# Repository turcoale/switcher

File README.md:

# switcher
Placa switcher, desarrollo de placa para automatización en instalaciones de frio

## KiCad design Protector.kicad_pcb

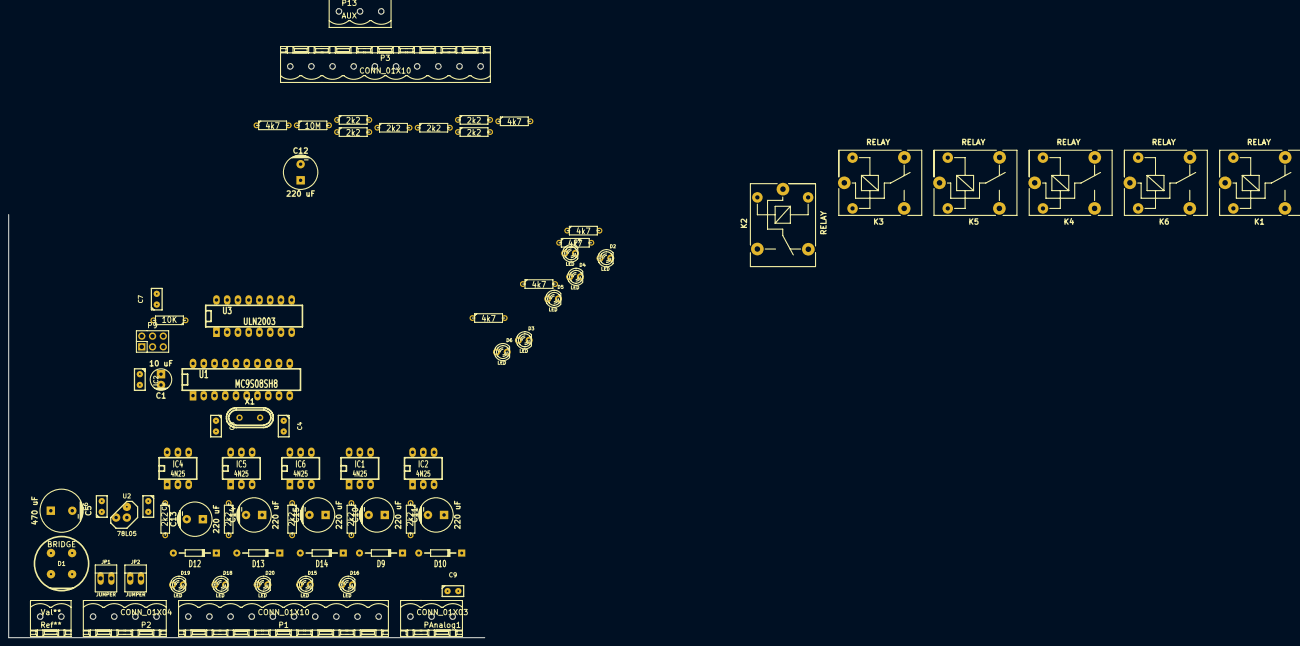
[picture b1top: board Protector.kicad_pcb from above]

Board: 2 copper layers, 75 parts (0 on the bottom side), 58 nets, no tracks yet.

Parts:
C1: 10 uF; Capacitor5x11RM2.5
C2, C9: 0,1 uF; Capacitor3MMDiscRM2.5
C3, C4: 22 nF; Capacitor3MMDiscRM2.5
C5: 470 uF; Capacitor10x16RM5
C6: 0.33 uF; Capacitor3MMDiscRM2.5
C7: 0.1 uF; Capacitor3MMDiscRM2.5
C8: 0.01 uF; Capacitor3MMDiscRM2.5
C10, C11, C12, C13, C14, C15: 220 uF; Capacitor8x21RM3.8
D1: BRIDGE; PUSH_BUTT_SHAPE1
D2, D3, D4, D5, D6, D7, D15, D16, D18, D19, D20: LED; LED-3MM
D9, D10, D12, D13, D14: 1N4001; Diode_DO-35_SOD27_Horizontal_RM10
IC1, IC2, IC4, IC5, IC6: 4N25; DIP-6__300_ELL
JP1, JP2: JUMPER; PINHEAD1-2
K1, K2, K3, K4, K5, K6: RELAY; Relay_SANYOU_SRD_Series_Form_C
P1, P3: CONN_01X10; PHOENIX_MSTBA2,54-G_10
P2: CONN_01X04; PHOENIX_MSTBA2,54-G_4
P9: BDM; Pin_Header_Straight_2x03
P13: AUX; PHOENIX_MSTBA2,54-G_3
PAnalog1: CONN_01X03; PHOENIX_MSTBA2,54-G_3
R1, R2, R4, R5, R6, R14, R15, R16, R17, R18, R19: 2k2; R3
R7, R8, R9, R10, R11, R12: 4k7; R3
R13: 10K; R3
R21: 10M; R3
Ref**: Val**; PHOENIX_MSTBA2,54-G_2
U1: MC9S08SH8; DIP-20__300_ELL
U2: 78L05; TO92-123
U3: ULN2003; DIP-16__300_ELL
X1: CRYSTAL; Crystal_HC49-U_Vertical

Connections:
/24Sen: JP1.1, P2.4, R4.2, R5.2, R6.2
/24V: C5.1, C6.1, D1.3, D2.1, D3.1, D4.1, D5.1, D6.1, D7.1, JP1.2, K1.2, K2.2, K3.2, K4.2, K5.2, K6.2, P2.2, U2.3, U3.9
/ADC: C9.1, PAnalog1.2, U1.19
/BDM: P9.1, U1.10
/COMSen: JP2.1, P1.1, P1.3, P1.5, P1.7, P1.9, P2.3
/EXTAL: C4.1, R21.1, U1.7, X1.2
/In1: IC4.5, R10.2
/In2: IC5.5, R11.2, U1.11
/In3: IC6.5, R12.2, U1.12
/In4: IC1.5, R7.2, U1.13
/In5: IC2.5, R8.2, U1.18
/OPT1: C13.2, D12.1, D19.2, IC4.2, P1.10
/OPT2: C14.2, D13.1, D18.2, IC5.2, P1.8
/OPT3: C15.2, D14.1, D20.2, IC6.2, P1.6
/OPT4: C10.2, D9.1, D15.2, IC1.2, P1.4
/OPT5: C11.2, D10.1, D16.2, IC2.2, P1.2
/Out1: U1.14, U3.6
/Out2: U1.15, U3.5
/Out3: U1.16, U3.4
/Out4: U1.17, U3.3
/Out5: U1.4, U3.2
/OutAux: U1.5, U3.1
/R1: K2.5, R15.2, U3.15
/R2: K3.5, R16.2, U3.14
/R3: K4.5, R17.2, U3.13
/R4: K5.5, R18.2, U3.12
/R5: K6.5, R19.2, U3.11
/RAUX: K1.5, R14.2, U3.16
/RESET: C7.1, P9.4, R13.2
/XTAL: C3.1, R21.2, U1.6, X1.1
/vreg: C1.1, C2.1, C8.1, P9.6, PAnalog1.3, R7.1, R8.1, R9.1, R10.1, R11.1, R12.1, R13.1, U1.9, U2.1
GND: C1.2, C2.2, C3.2, C4.2, C5.2, C6.2, C7.2, C8.2, C9.2, D1.2, IC1.4, IC2.4, IC4.4, IC5.4, IC6.4, JP2.2, P2.1, P9.2, PAnalog1.1, U1.8, U2.2, U3.8
unnamed: D1.1, Ref**.2
unnamed: D1.4, Ref**.1
unnamed: D2.2, R14.1
unnamed: D3.2, R15.1
unnamed: D4.2, R16.1
unnamed: D5.2, R17.1
unnamed: D6.2, R18.1
unnamed: D7.2, R19.1
unnamed: D15.1, IC1.1, R1.1
unnamed: D16.1, IC2.1, R2.1
unnamed: D18.1, IC5.1, R5.1
unnamed: D19.1, IC4.1, R4.1
unnamed: D20.1, IC6.1, R6.1
unnamed: K1.1, P13.2
unnamed: K1.3, P13.1
unnamed: K1.4, P13.3
unnamed: K2.1, P3.1
unnamed: K2.4, P3.2
unnamed: K3.1, P3.3
unnamed: K3.4, P3.4
unnamed: K4.1, P3.5
unnamed: K4.4, P3.6
unnamed: K5.3, P3.7
unnamed: K5.4, P3.8
unnamed: K6.1, P3.9
unnamed: K6.4, P3.10

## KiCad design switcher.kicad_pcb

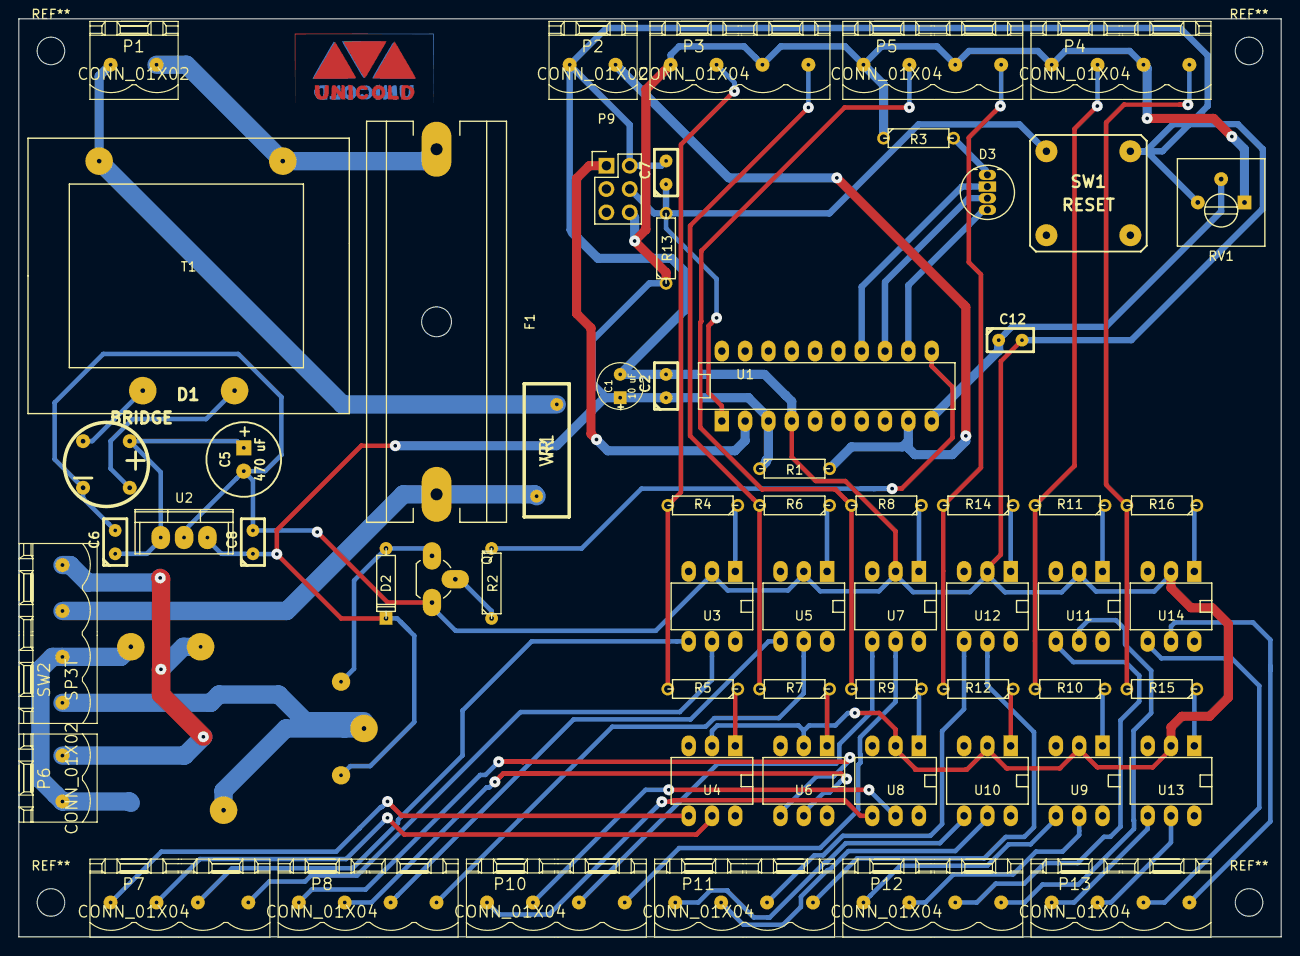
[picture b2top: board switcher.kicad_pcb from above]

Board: 2 copper layers, 137.5 x 100.0 mm, 61 parts (1 on the bottom side), 64 nets.

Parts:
C1: 10 uF; C1V5
C2, C12: 0,1 uF; C1
C5: 470 uF; C1V8
C6: 0.33 uF; C1
C7: 0.1 uF; C1
C8: 0.01 uF; C1
D1: BRIDGE; Bridge-rond
D2: 1N4001; D3
D3: Led_RGB_CA; LED-RGB-5MM_Common_Cathode
F1: FUSE; Fuseholder6x32_Horiz_Open_Schurter0031-8002
K1: RELAY; RELAY-HJQ-15F
P1, P2, P6: CONN_01X02; PHOENIX_MSTBA2,54-G_2
P3, P4, P5, P7, P8, P10, P11, P12, P13: CONN_01X04; PHOENIX_MSTBA2,54-G_4
P9: BDM; Pin_Header_Straight_2x03
Q1: BC237; TO-92_Rugged
R1: 10k; R3
R2, R3: 1k; R3
R4, R5, R6, R7, R8, R9, R10, R11, R12, R14, R15, R16: 220; R3
R13: 10K; R3
RV1: POT; Potentiometer_Trimmer-Suntan-TSR-3386P
SW1: RESET; sw_push4p
SW2: SP3T; PHOENIX_MSTBA2,54-G_4
T1: TRANSFO; TFCOBSIL2209VCA200mA
U1: MC9S08SH8; DIP-20__300_ELL
U2: 78L05; TO-220
U3, U4, U5, U6, U7, U8, U9, U10, U11, U12, U13, U14: 4N25; DIP-6__300_ELL
VR1: VR; SIOV-S20K150

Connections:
/24V: C5.1, C6.1, D1.3, U2.1
/BDM: P9.1, U1.2
/C: K1.3, K1.6, SW2.1
/F1: F1.2, SW2.3, VR1.1
/L: F1.1, P1.2, T1.1
/N: P1.1, T1.2, VR1.2
/NA: K1.2, P6.2, SW2.4
/NC: K1.1, P6.1, SW2.2
/RESET: C7.1, P9.4, R13.2, SW1.1, U1.1
/ST: C12.1, RV1.2, U1.10
/vreg: C1.1, C2.1, C8.1, D2.1, K1.5, P3.1, P3.3, P4.1, P4.3, P5.1, P5.3, P9.6, R1.1, R3.1, R13.1, RV1.1, U1.3, U2.3
GND: C1.2, C2.2, C5.2, C6.2, C7.2, C8.2, C12.2, D1.1, P2.1, P9.2, Q1.3, RV1.3, SW1.2, U1.4, U2.2, U3.2, U4.2, U5.2, U6.2, U7.2, U8.2, U9.2, U10.2, U11.2, U12.2, U13.2, U14.2
unnamed: D1.2, T1.3
unnamed: D1.4, T1.4
unnamed: D2.2, K1.4, Q1.1
unnamed: D3.1, R3.2
unnamed: D3.2, U1.14
unnamed: D3.3, U1.13
unnamed: D3.4, U1.12
unnamed: P2.2, R1.2, U1.9
unnamed: P3.4, R6.2, R7.2
unnamed: P3.2, R4.2, R5.2
unnamed: P4.4, R15.2, R16.2
unnamed: P4.2, R10.2, R11.2
unnamed: P5.4, R12.2, R14.2
unnamed: P5.2, R8.2, R9.2
unnamed: P7.4, U3.5
unnamed: P7.3, U3.4
unnamed: P7.2, U4.5
unnamed: P7.1, U4.4
unnamed: P8.4, U5.5
unnamed: P8.3, U5.4
unnamed: P8.2, U6.5
unnamed: P8.1, U6.4
unnamed: P10.4, U7.5
unnamed: P10.3, U7.4
unnamed: P10.2, U8.5
unnamed: P10.1, U8.4
unnamed: P11.2, U10.5
unnamed: P11.1, U10.4
unnamed: P11.4, U12.5
unnamed: P11.3, U12.4
unnamed: P12.1, U9.4
unnamed: P12.2, U9.5
unnamed: P12.3, U11.4
unnamed: P12.4, U11.5
unnamed: P13.2, U13.5
unnamed: P13.4, U14.5
unnamed: P13.3, U14.4
unnamed: Q1.2, R2.1
unnamed: R2.2, U1.11
unnamed: R4.1, U3.1
unnamed: R5.1, U4.1
unnamed: R6.1, U5.1
unnamed: R7.1, U6.1
unnamed: R8.1, U7.1
unnamed: R9.1, U8.1
unnamed: R10.1, U9.1
unnamed: R11.1, U11.1
unnamed: R12.1, U10.1
unnamed: R14.1, U12.1
unnamed: R15.1, U13.1
unnamed: R16.1, U14.1
unnamed: P13.1, U13.4

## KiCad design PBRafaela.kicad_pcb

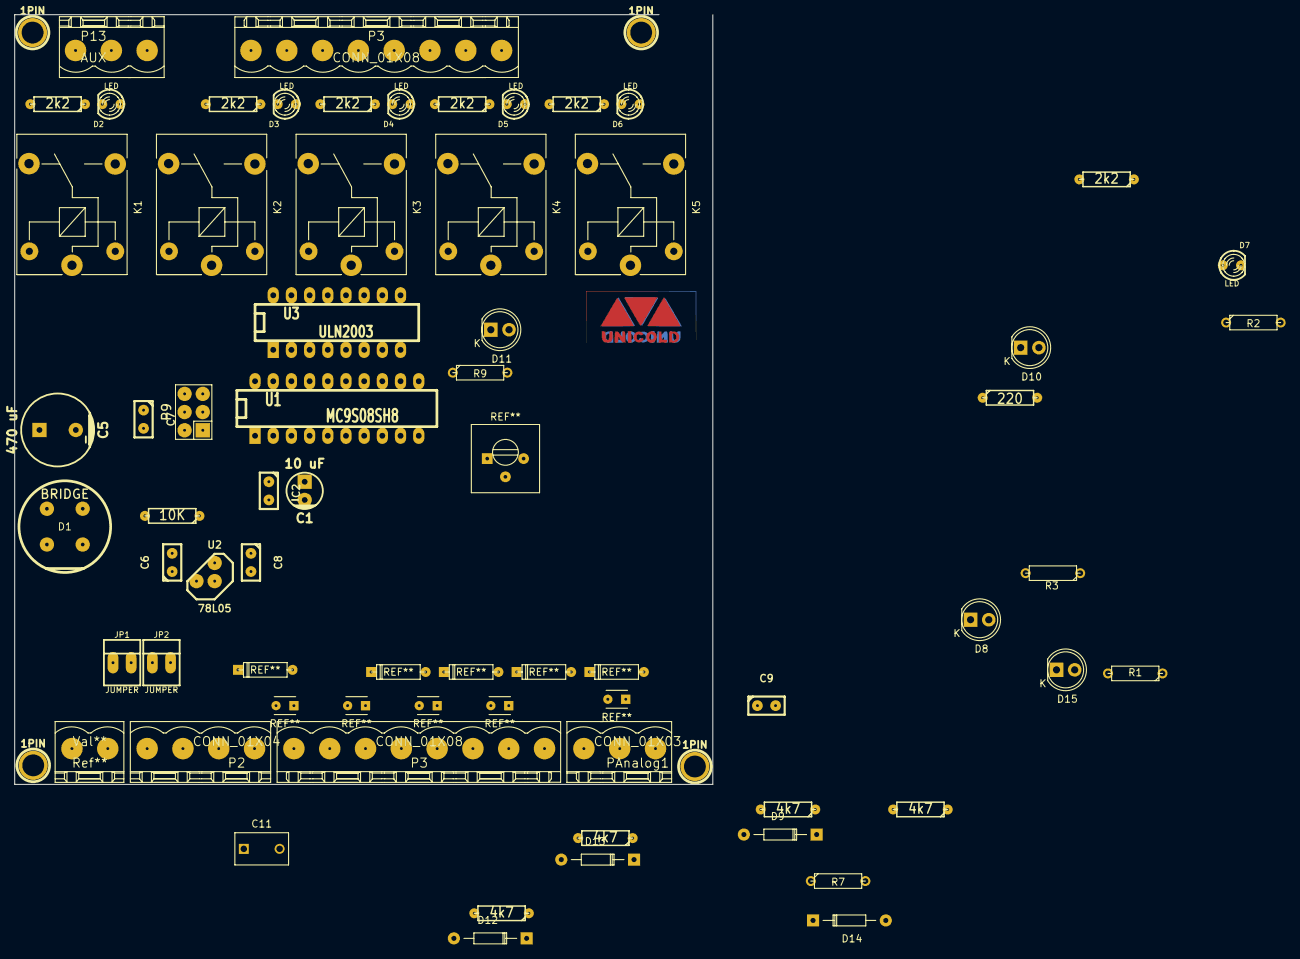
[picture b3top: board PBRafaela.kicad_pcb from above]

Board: 2 copper layers, 97.5 x 107.5 mm, 61 parts (0 on the bottom side), 58 nets, no tracks yet.

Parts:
1PIN, 1PIN#2, 1PIN#3, 1PIN#4: P***; 1pin
C1: 10 uF; Capacitor5x11RM2.5
C2, C9: 0,1 uF; Capacitor3MMDiscRM2.5
C5: 470 uF; Capacitor10x16RM5
C6: 0.33 uF; Capacitor3MMDiscRM2.5
C7: 0.1 uF; Capacitor3MMDiscRM2.5
C8: 0.01 uF; Capacitor3MMDiscRM2.5
C11: C; C_Disc_D7.5_P5
D1: BRIDGE; PUSH_BUTT_SHAPE1
D2, D3, D4, D5, D6, D7: LED; LED-3MM
D8, D10, D11, D15: LED; LED-5MM
D9, D12, D13, D14: DIODE; Diode_DO-35_SOD27_Horizontal_RM10
JP1, JP2: JUMPER; PINHEAD1-2
K1, K2, K3, K4, K5: RELAY; Relay_SANYOU_SRD_Series_Form_C
P2: CONN_01X04; PHOENIX_MSTBA2,54-G_4
P3, P3#2: CONN_01X08; PHOENIX_MSTBA2,54-G_10
P9: BDM; Pin_Header_Straight_2x03
P13: AUX; PHOENIX_MSTBA2,54-G_3
PAnalog1: CONN_01X03; PHOENIX_MSTBA2,54-G_3
R1, R2, R3, R8, R9: 220; R3
R7, R8#2, R10, R11, R12: 4k7; R3
R13: 10K; R3
R14, R15, R16, R17, R18, R19: 2k2; R3
Ref**: Val**; PHOENIX_MSTBA2,54-G_2
U1: MC9S08SH8; DIP-20__300_ELL
U2: 78L05; TO92-123
U3: ULN2003; DIP-16__300_ELL

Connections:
/24Sen: JP1.1, P2.4
/24V: C5.1, C6.1, D1.3, D2.1, D3.1, D4.1, D5.1, D6.1, JP1.2, P2.2, U3.9
/ADC: C9.1, PAnalog1.2, U1.11
/BDM: P9.1, U1.2
/COMSen: JP2.1, P2.3, P3.1, P3.3, P3.5, P3.7
/In1: R10.2, U1.20
/In2: R11.2, U1.19
/In3: R12.2, U1.18
/In4: R7.2, U1.17
/LED1: D7.1, U1.5
/LED2: D8.1, U1.6
/LED3: D10.1, U1.8
/LED4: D15.1, U1.10
/LED_SP: D11.1, U1.12
/OPT1: D9.2, P3.8
/OPT2: C11.1, D12.2, P3.6
/OPT3: D13.2, P3.4
/OPT4: D14.2, P3.2
/Out1: U1.16, U3.2
/Out2: U1.15, U3.3
/Out3: U1.14, U3.4
/Out4: U1.13, U3.5
/OutAux: U1.7, U3.1
/R1: R15.2, U3.15
/R2: R16.2, U3.14
/R3: R17.2, U3.13
/R4: R18.2, U3.12
/RAUX: R14.2, U3.16
/RESET: C7.1, P9.4, R13.2, U1.1
/vreg: C1.1, C2.1, C8.1, P9.6, PAnalog1.3, R13.1, U1.3
GND: C1.2, C2.2, C5.2, C6.2, C7.2, C8.2, C9.2, C11.2, D1.1, JP2.2, P2.1, P9.2, PAnalog1.1, R1.1, R2.1, R3.1, R8.1, R9.1, U1.4, U3.8
unnamed: D1.2, Ref**.2
unnamed: D1.4, Ref**.1
unnamed: D2.2, R14.1
unnamed: D3.2, R15.1
unnamed: D4.2, R16.1
unnamed: D5.2, R17.1
unnamed: D6.2, R18.1
unnamed: D7.2, R2.2, R19.1
unnamed: D8.2, R3.2
unnamed: D9.1, R10.1
unnamed: D10.2, R8.2
unnamed: D11.2, R9.2
unnamed: D12.1, R11.1
unnamed: D13.1, R12.1
unnamed: D14.1, R7.1
unnamed: D15.2, R1.2
unnamed: K1.1, P13.2
unnamed: K1.3, P13.3
unnamed: K1.4, P13.1
unnamed: K2.1, P3#2.2
unnamed: K2.3, P3#2.1
unnamed: K3.1, P3#2.4
unnamed: K3.3, P3#2.3
unnamed: K4.1, P3#2.6
unnamed: K4.3, P3#2.5
unnamed: K5.1, P3#2.8
unnamed: K5.3, P3#2.7

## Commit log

2015-11-25 archivos
2015-11-25 cambio relay
2016-01-11 finalizado
2016-01-11 leeme
2016-01-12 di vueltas el relay
2016-01-18 commit de seguridad
2016-02-29 ultimo commit febrero
